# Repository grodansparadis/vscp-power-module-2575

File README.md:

# vscp-power-module-2575
VSCP Power module

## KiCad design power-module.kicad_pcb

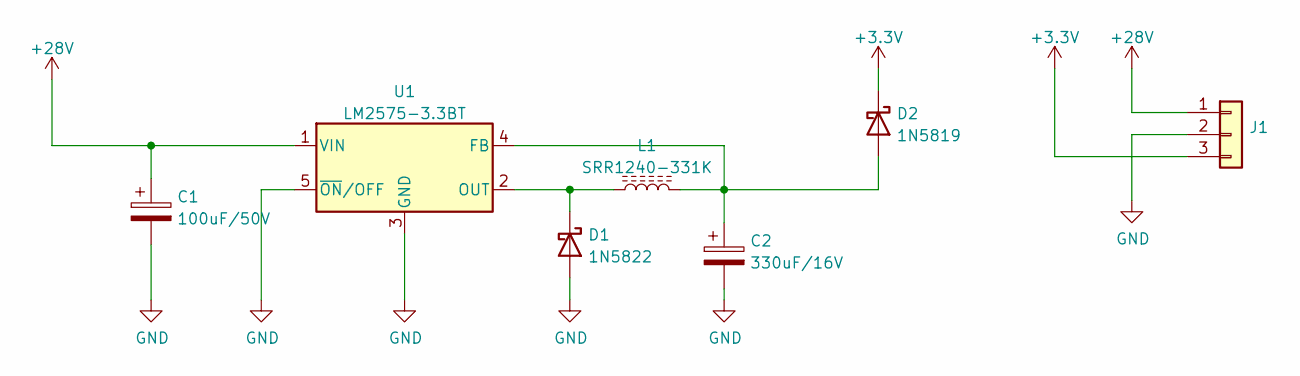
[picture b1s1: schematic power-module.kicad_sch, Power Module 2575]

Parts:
C1: 100uF/50V; CP_Elec_6.3x9.9
C2: 330uF/16V; CP_Elec_6.3x9.9
D1: 1N5822; D_SMA_Handsoldering
D2: 1N5819; D_SOD-123
J1: Conn_01x03; PinHeader_1x03_P2.54mm_Vertical
L1: SRR1240-331K; L_Bourns_SRR1260
U1: LM2575-3.3BT; TO-263-5_TabPin3

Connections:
+3V3: D2.1 (K), J1.3
+28V: C1.1, J1.1, U1.1 (VIN)
GND: C1.2, C2.2, D1.2 (A), J1.2, U1.3 (GND), U1.5 (~ON/OFF)
unnamed: D1.1 (K), L1.1, U1.2 (OUT)
unnamed: C2.1, D2.2 (A), L1.2, U1.4 (FB)

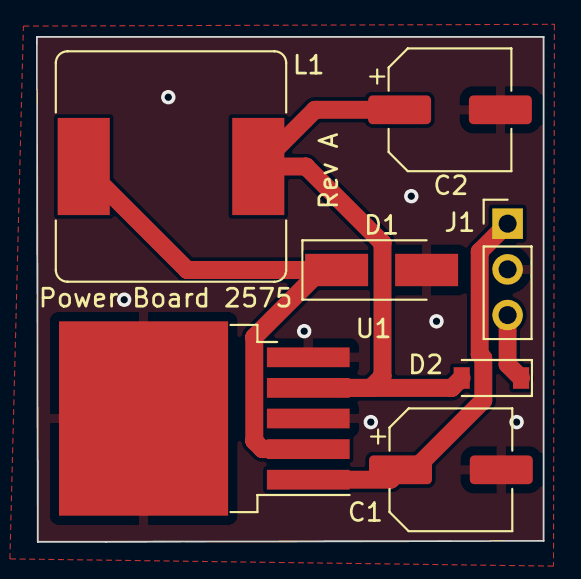
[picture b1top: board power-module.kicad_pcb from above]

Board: 2 copper layers, 28.2 x 28.0 mm, 7 parts (0 on the bottom side), 5 nets.

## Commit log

2022-09-05 Initial checkin
2022-09-05 Added images to readme
2022-09-05 Gerbers added
